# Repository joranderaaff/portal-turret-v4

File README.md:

# Portal Turret v4

A Portal-style turret powered by an ESP32-S3 (Lolin S3 Mini). It detects people with a mmWave radar, opens its wings, extends its guns and tracks targets, complete with sound and lights.

## Repository layout

| Folder | Contents |
| --- | --- |
| `src/` | Firmware (PlatformIO, Arduino framework) |
| `data/` | LittleFS image: audio clips and web UI |
| `3d/` | 3D model (`model.step`) |
| `gerber/` | PCB manufacturing files (MainBoard, DaughterBoard) |
| `images/` | Build guide photos |

## Bill of materials

### Printing
- PLA (Or other material) in white, black and optionally transparent.

### Electronics
- Lolin Wemos S3 Mini
- 4x SG90 180 servo
- 2x SG90 360 servo
- LD2450 Radar Sensor
- ADXL345 Digital 3-axis Accelerometer Module
- MAX98357 Audio amp
- 2x OH49E Hall Effect Sensor - SS49E compatible
- SN74AHCT125N 4-channel Level Converter
- SK6812 Digital 5050 RGB LED Ring
- 5x WS2812 5mm LED
- Small rocker switch
- USB C Breakout Board, 12 * 15 * 1.6mm
- 2x 100nF Ceramic Capacitor 
- 1x 100uF 25V Elektrolytic Capacitor

### Motion
- 604ZZ Ball Bearing - 4x12x4mm
- MYT LM6LUU Linear Ball Bearing - 2 pieces (35mm length)
- 4mm steel rod
- 6mm steel rod

### Cables
- JST PH crimp set OR JST PH headers and pre-crimped JST PH cables
- Pin headers

### Fasteners
- 2mm wood screws
- Super Glue

## Steel Rod Sizes

For the 4mm rods:
- 1x 150mm (enforcing the rear leg)
- 2x 55mm (enforcing the front legs)
- 2x 60mm (wings)
- 1x 43mm (x-axis axle)
- 1x 20mm (z-axis bottom axle)
- 1x 10mm (z-axis top axle)

The bended rods for the legs do not have a very precise length. It's best to bend and cut to length after bending, as this makes the process of getting the correct shape a lot easier.

For the 6mm rods:
- 2x 60mm (wings)

## 3D printing

STEP file contains all 3D printed parts.

[All STL files can be found here.](https://www.printables.com/model/1892132-portal-turret-mk-ii)

## Electronics

Gerber files are included. Order from your favorite PCB manufacturer.

### Pinout

ESP32-S3 GPIO numbers, defined in `src/pins.h`.

| Function | GPIO |
| --- | --- |
| Left / right gun servo | 1 / 2 |
| Left / right wing servo | 4 / 5 |
| Rotate X / Z servo | 6 / 7 |
| Left / right hall sensor (analog) | 8 / 9 |
| Eye LED ring (center) / left gun LEDs / right gun LEDs | 14 / 15 / 16 |
| Radar (ESP RX / ESP TX) | 17 / 18 |
| ADXL345 I2C (SDA / SCL) | 35 / 36 |
| Audio amp I2S (DIN / BCLK / LRCLK) | 10 / 11 / 12 |

### Power

The turret runs on 5 V, from the USB-C board or the power connector. The servos, LED ring, audio amp and radar all share it, so use a supply that can deliver at least 2 A. That figure is a rule of thumb for six SG90 servos plus the LEDs, not a measured value.

## Preperation

The 180 degree servos might not be centered when you purchase them. Make sure you to do this with a servo tester or writing a small Arduino sketch that centers your servos. If you don't have an Arduino board to do this, you could even use the Wemos in a breadboard and use some wires to hook up a servo to calibrate them.

Use the hall sensor to find out what the north and south pole of your magnets are. You'll need to know this to make sure you insert them correctly later in the build.
Again you can use the Wemos to test. Using a breadboard, hook up the sensor to 3.3V, Gnd and one of the analog pins. Read the analog value. When the north pole faces the sensor, the value should increase. If it's the south pole, it should decrease.

## Assembly guide

Here's raw screenshots. Explicit information comes later.

### X axis

| Notes | Images |
| --- | --- |
| Screw the two halves together. |  |
| Insert the LM6LUU and 604ZZ bearings. Screw the gears on the two 360 servos. |  |
| Solder the wires to the hall sensors. Use shrink tubing to protect the leads. Insert the hall sensors into the slots. The beveled face is the front and should point towards the space where the rack gears will slide. |  | 
| Tuck the wires underneath the little lip. This should help with keeping the hall sensors in place. If they don't want to stay seated, a drop of superglue should help. |  | 

### Z axis
| Notes | Images |
| --- | --- |
| Screw on the X Axis gear on a 180 servo. Slide it in place and use the channels to screw it down. |  |
| Attach one side. |  |
| Slide a 4mm rod through the X axis. Add a 4mm shim on both sides. There is a slot in the frame where the rod should fit. |  |
| Scew on the bottom and the other side. |  |
| Use a ziptie to manage all cables. It should hold the following wires: 2 Hall sensors, 2 Wing servos, X Axis servo. |  |

### Bottom
| Notes | Images |
| --- | --- |
| Slide a 180 servo in the mount and screw it secure |  |
| Screw on the Z Axis gear. |  |
| The USB-C board should be glued into place. If you can't get a solid connection with glue, a tiny screw with some heatshrink could be screwed through the D- slot. Make sure the screw does not short D- to ground, hence the heatshrink tubing. Run the wires through the bottom. Make sure to leave enough to route the wires and attach the JST connector. |  |
| Route the two 5V wires to the bottom. One should come from the USB board, the other should go to your power connector. |  |
| The servo wires should also be run through the same channel to go up in the back. |  |
| Run both the servo and power wires through the gantry. Use the little brace to keep them out of the way from the gantry.  |  |

### Eye
| Notes | Images |
| --- | --- |
| Print the flat retina and mold. As PLA gets soft at relatively low temperatures, you can dunk it in boiling water and press it on the mold for the correct shape. Make sure to print the diffuser with very little top/bottom layers and walls, or use transparent filament. Glue in the LED ring and 5mm LED. Bend the 5V and Gnd legs of the LED to the pads of the ring and solder them together. The `D-in` leg should go to the `D-out` pad. Run 3 wires to the `D-in` `5V` and `Gnd` pads of the LED Ring. Keep enough length to run it through the turret. Add a JST connector when you're sure you have enough length. |  |

### Gantry

| Notes | Images |
| --- | --- |
| The gantry consists of 5 different pieces. This is done so you can print with little to no support material. The eye should click in place and stay there without any glue. |  |
| The whole gantry should screw together and give enough rigidity for the build. |  |
| Slide in the gantry and bottom. Make sure to not rotate your servo when assembling, otherwise you'll risk a very big offset in angle. You can calibrate small offsets in the settings. |  |
| Screw in the last screws on the front and back of the gantry to finish the motion system. |  |

### Guns

| Notes | Images |
| --- | --- |
| Prepare the LED harness. You can either use JST connectors or solder directly to the board. Make sure you double check the pads of the board and the legs of your LEDs. I've found that different brands can have a different order in the legs. Please note that the `Data In` leg should go to the `Data In` pad, NOT the `Data Out` pad. |  |
| Attach the lever to a 180 servo. The lever should be a friction fit. Insert it into the gun casing and run the wire as shown. Note that the LED harness is not shown here, but should already be attached to the board. |  |
| There's a hole in the bottom to fasten the servo with a screw. |  |
| Insert the barrels into their housing. This should be a friction fit. The housing screws on the part with one screw. |  |
| Slide in the bottom LED and run the wires to the side and through the clamp in the front. |  |
| Slide in the top LED and run the wires out the top. |  |
| Rotate the lever so it points forward. |  |
| Carefully slide the barrels over the lever. You might need to bend the housing to get it in place. Note that the pictures shows the wires outside of the clamps, this is a render error. |  |
| Slide the barrels back into the housing. They should slide easily. If not, try to move the lever by hand. If the barrels don't move, check the clearance of your parts. |  |
| The top can now be screwed on. |  |
| The front plate should click in place. |  |

### Wings

| Notes | Images |
| --- | --- |
| Add 1mm magnets to the slots of the wing. Mind the polarity! |  |
| Add 1mm magnets to the slots of the the wing frame. Mind the polarity! |  |
| The gun should slide in the designated slot. |  |
| Insert the magnets in the rack gear. They should click in place, but a drop of glue helps. Make sure to mind the polarity!|  |
| Attach the rack gear and secure it with a screw. Glue in the 4mm and 6mm steel rods. |  |

### PCB, Speaker and Radar

| Notes | Images |
| --- | --- |
| PCB, Speaker and Radar should be mounted in the top. Note that the ADXL and Amplifier are missing in this picture. They should be soldered on the PCB. |  |
| There are optional panels to cover the electronics. |  |

### Leg
| Notes | Images |
| --- | --- |
| The legs should be glued together. Use a piece of 4mm rod to strengthen the joint between the "leg" and the "knee" |  |

## Firmware

You can build the firmware with <a href="https://code.visualstudio.com/">Visual Studio Code</a> together with the PlatformIO plugin.

Use the following two commands to flash your Wemos:

Or use these commands if you prefer working in the terminal.

```bash
pio run                # build
pio run -t upload      # flash firmware
pio run -t uploadfs    # flash LittleFS (audio + web UI)
```

Flash both on a new turret: the firmware first, then the filesystem. Run `uploadfs` again whenever something in `data/` changes.

OTA updates are possible once the turret is on your network (`turret.local`) or in its own access point ("Portal Turret", `192.168.4.1`). While an update runs the turret stops moving and the audio pauses.

### First start and WiFi

1. On the first start, and whenever the turret can't join its saved network, it opens the WiFi network "Portal Turret".
2. Connect to it. The WiFi setup page opens by itself, or browse to `http://192.168.4.1`.
3. Pick your network and enter the password. The turret restarts, joins your network and is reachable at `http://turret.local`.
4. If the saved network is out of reach (for example the router is still booting after a power cut), the "Portal Turret" network returns. The turret tries the saved network again every minute, as long as nobody is connected to its access point, and closes the access point once it is back on your network.

The access point is open by default. To protect it, enter 8 or more characters as "Access Point Password" on the Settings page and restart the turret. The access point keeps that password when you reset the settings to their defaults, so it can't fall back to open by accident.

### Web interface

| Page | What it does |
| --- | --- |
| Home | Live radar, accelerometer graphs and the turret's message log. |
| Control | Start the turret by hand. |
| Remote | Aim with a joystick, open/close the wings, fire, party mode. |
| Settings | All settings, Restart, reset to defaults, enable multitarget on the radar. |
| WiFi | Pick the network the turret joins. |
| Diagnose | Move every servo raw, read the hall sensors, test LEDs and audio. |

Settings take effect as soon as you save them. Only the network settings (WiFi, access point password) need a restart: use the Restart button on the Settings page.

Remote and Diagnose stop all automatic behaviour. Press Resume on either page to hand control back: the turret centers the gantry, closes the wings and starts over. A power cycle does the same.

## Calibration

When connecting to the web portal, there is a `Settings` page. Most of these settings are tweaked already, but you might need a few to get your turret to work perfectly:
You can use the `Diagnose` page to find the exact values you want to use (the hall sensor readings help with Gun Hall Min/Max).

- Angle offset X: Use this to make sure the wings are pointing forward when the turret is idle.
- Angle offset Z: Use this to center the gantry when the turret is idle.
- Gun Hall Min/Max: The treshold of the hall sensor that triggers the Open/Closed state of the wings.

The other parameters are less important, but you can play around with them to suit your needs.

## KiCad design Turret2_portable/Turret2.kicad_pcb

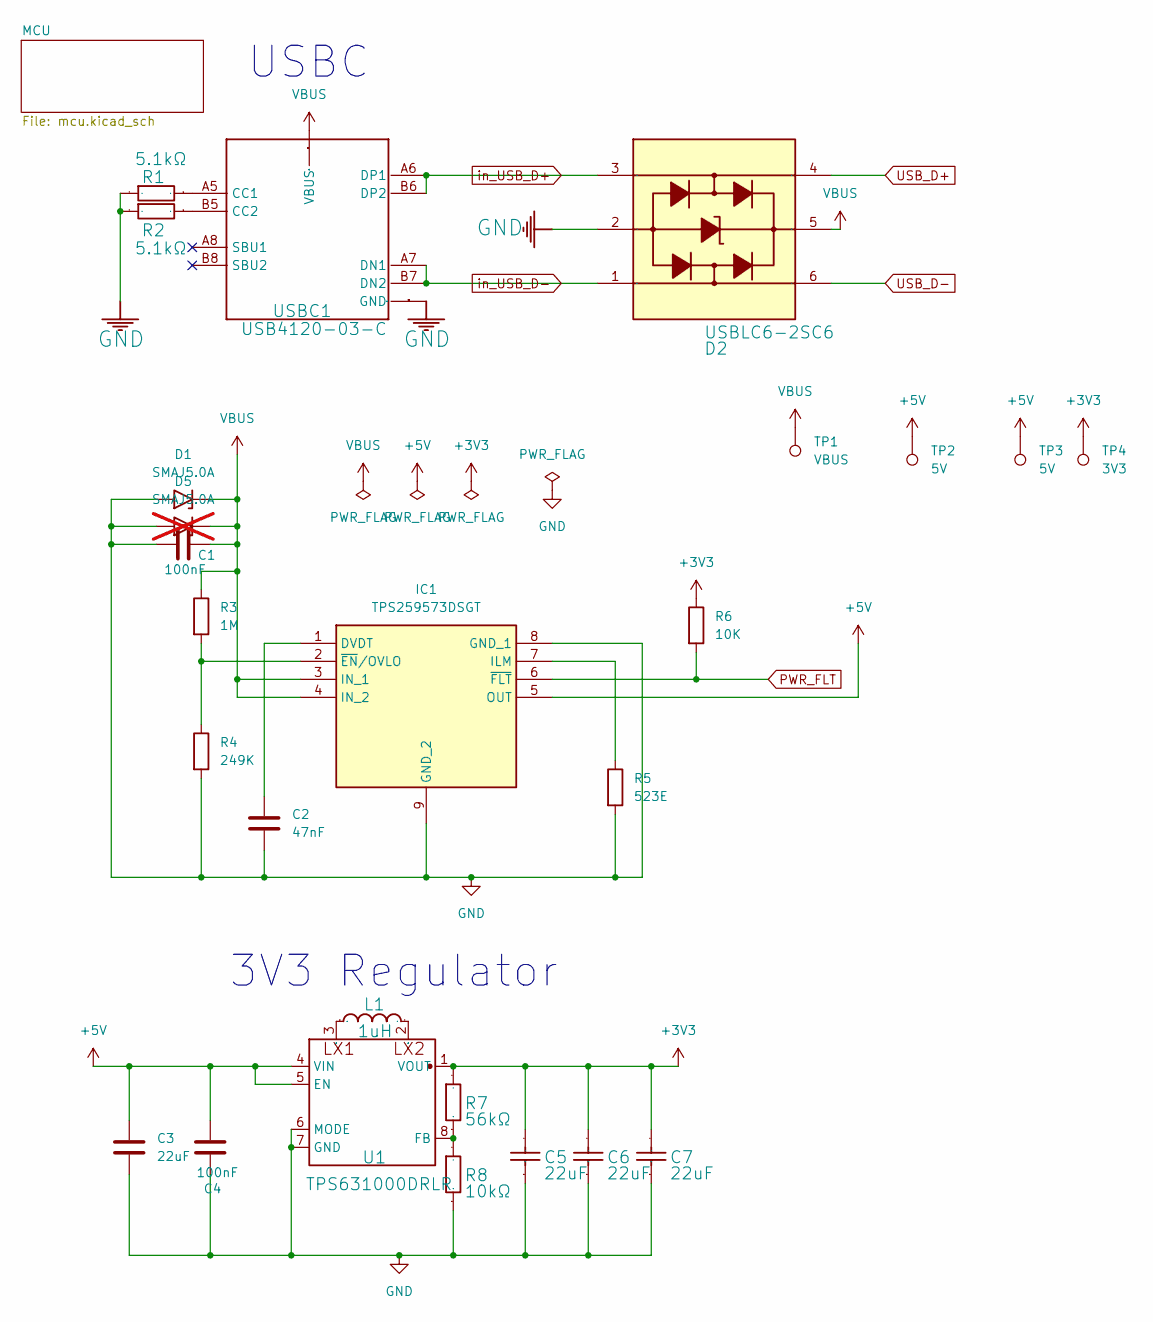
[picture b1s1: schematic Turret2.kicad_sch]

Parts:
C1, C4: 100nF; C_0603_1608Metric
C2: 47nF; C_0603_1608Metric
C3: 22uF; C_1210_3225Metric
C5, C6, C7: 22uF; C_1210_3225Metric; Manufacturer Part MCAST32MSB7226KPNA01
D1: SMAJ5.0A; D_SMA
D2: USBLC6-2SC6; SOT-23-6; Manufacturer Part USBLC6-2SC6
D5: SMAJ5.0A; D_SMA; not fitted
IC1: TPS259573DSGT; Texas_DSG0008A_WSON-8-1EP_2x2mm_P0.5mm_EP0.9x1.6mm_ThermalV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; Mouser Part Number 595-TPS259573DSGT
L1: 1uH; L_Changjiang_FTC303020D; Manufacturer Part FTC303020D1R0MBCA
R1, R2: 5.1kΩ; R_0603_1608Metric; Manufacturer Part 0402WGF5101TCE
R3: 1M; R_0603_1608Metric
R4: 249K; R_0603_1608Metric
R5: 523E; R_0603_1608Metric
R6: 10K; R_0603_1608Metric
R7: 56kΩ; R_0603_1608Metric; Manufacturer Part 0603WAF5602T5E
R8: 10kΩ; R_0603_1608Metric; Manufacturer Part 0402WGF1002TCE
TP1: VBUS; TestPoint_Pad_D1.0mm
TP2, TP3: 5V; TestPoint_Pad_D1.0mm
TP4: 3V3; TestPoint_Pad_D1.0mm
U1: TPS631000DRLR; SOTFL50P160X60-8N; Manufacturer Part TPS631000DRLR
USBC1: USB4120-03-C; USB412003C; Manufacturer Part USB4120-03-C

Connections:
+3V3: C5.2, C6.2, C7.2, R6.1, R7.2, TP4.1 (1_1), U1.1 (VOUT); also elsewhere on the board
+5V: C3.1, C4.1, IC1.5 (OUT), TP2.1 (1_1), TP3.1 (1_1), U1.4 (VIN), U1.5 (EN); also elsewhere on the board
GND: C1.1, C2.2, C3.2, C4.2, C5.1, C6.1, C7.1, D1.2 (A2), D2.2, D5.2 (A2), IC1.8 (GND_1), IC1.9 (GND_2), R1.2, R2.2, R4.2, R5.2, R8.1, U1.6 (MODE), U1.7 (GND), USBC1.A1 (GND), USBC1.A12 (GND), USBC1.B1 (GND), USBC1.B12 (GND), USBC1.MH1 (GND), USBC1.MH2 (GND), USBC1.MH3 (GND), USBC1.MH4 (GND); also elsewhere on the board
unnamed: C2.1, IC1.1 (DVDT)
unnamed: IC1.7 (ILM), R5.1
unnamed: IC1.2 (~EN/OVLO), R3.2, R4.1
unnamed: R7.1, R8.2, U1.8 (FB)
unnamed: L1.1, U1.3 (LX1)
unnamed: L1.2, U1.2 (LX2)
unnamed: R1.1, USBC1.A5 (CC1)
unnamed: R2.1, USBC1.B5 (CC2)
PWR_FLT: IC1.6 (~FLT), R6.2; also elsewhere on the board
USB_D+: D2.4; also elsewhere on the board
USB_D-: D2.6; also elsewhere on the board
VBUS: C1.2, D1.1 (A1), D2.5, D5.1 (A1), IC1.3 (IN_1), IC1.4 (IN_2), R3.1, TP1.1 (1_1), USBC1.A4 (VBUS), USBC1.A9 (VBUS), USBC1.B4 (VBUS), USBC1.B9 (VBUS); also elsewhere on the board
in_USB_D+: D2.3, USBC1.A6 (DP1), USBC1.B6 (DP2); also elsewhere on the board
in_USB_D-: D2.1, USBC1.A7 (DN1), USBC1.B7 (DN2); also elsewhere on the board

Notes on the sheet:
3V3 Regulator
USBC

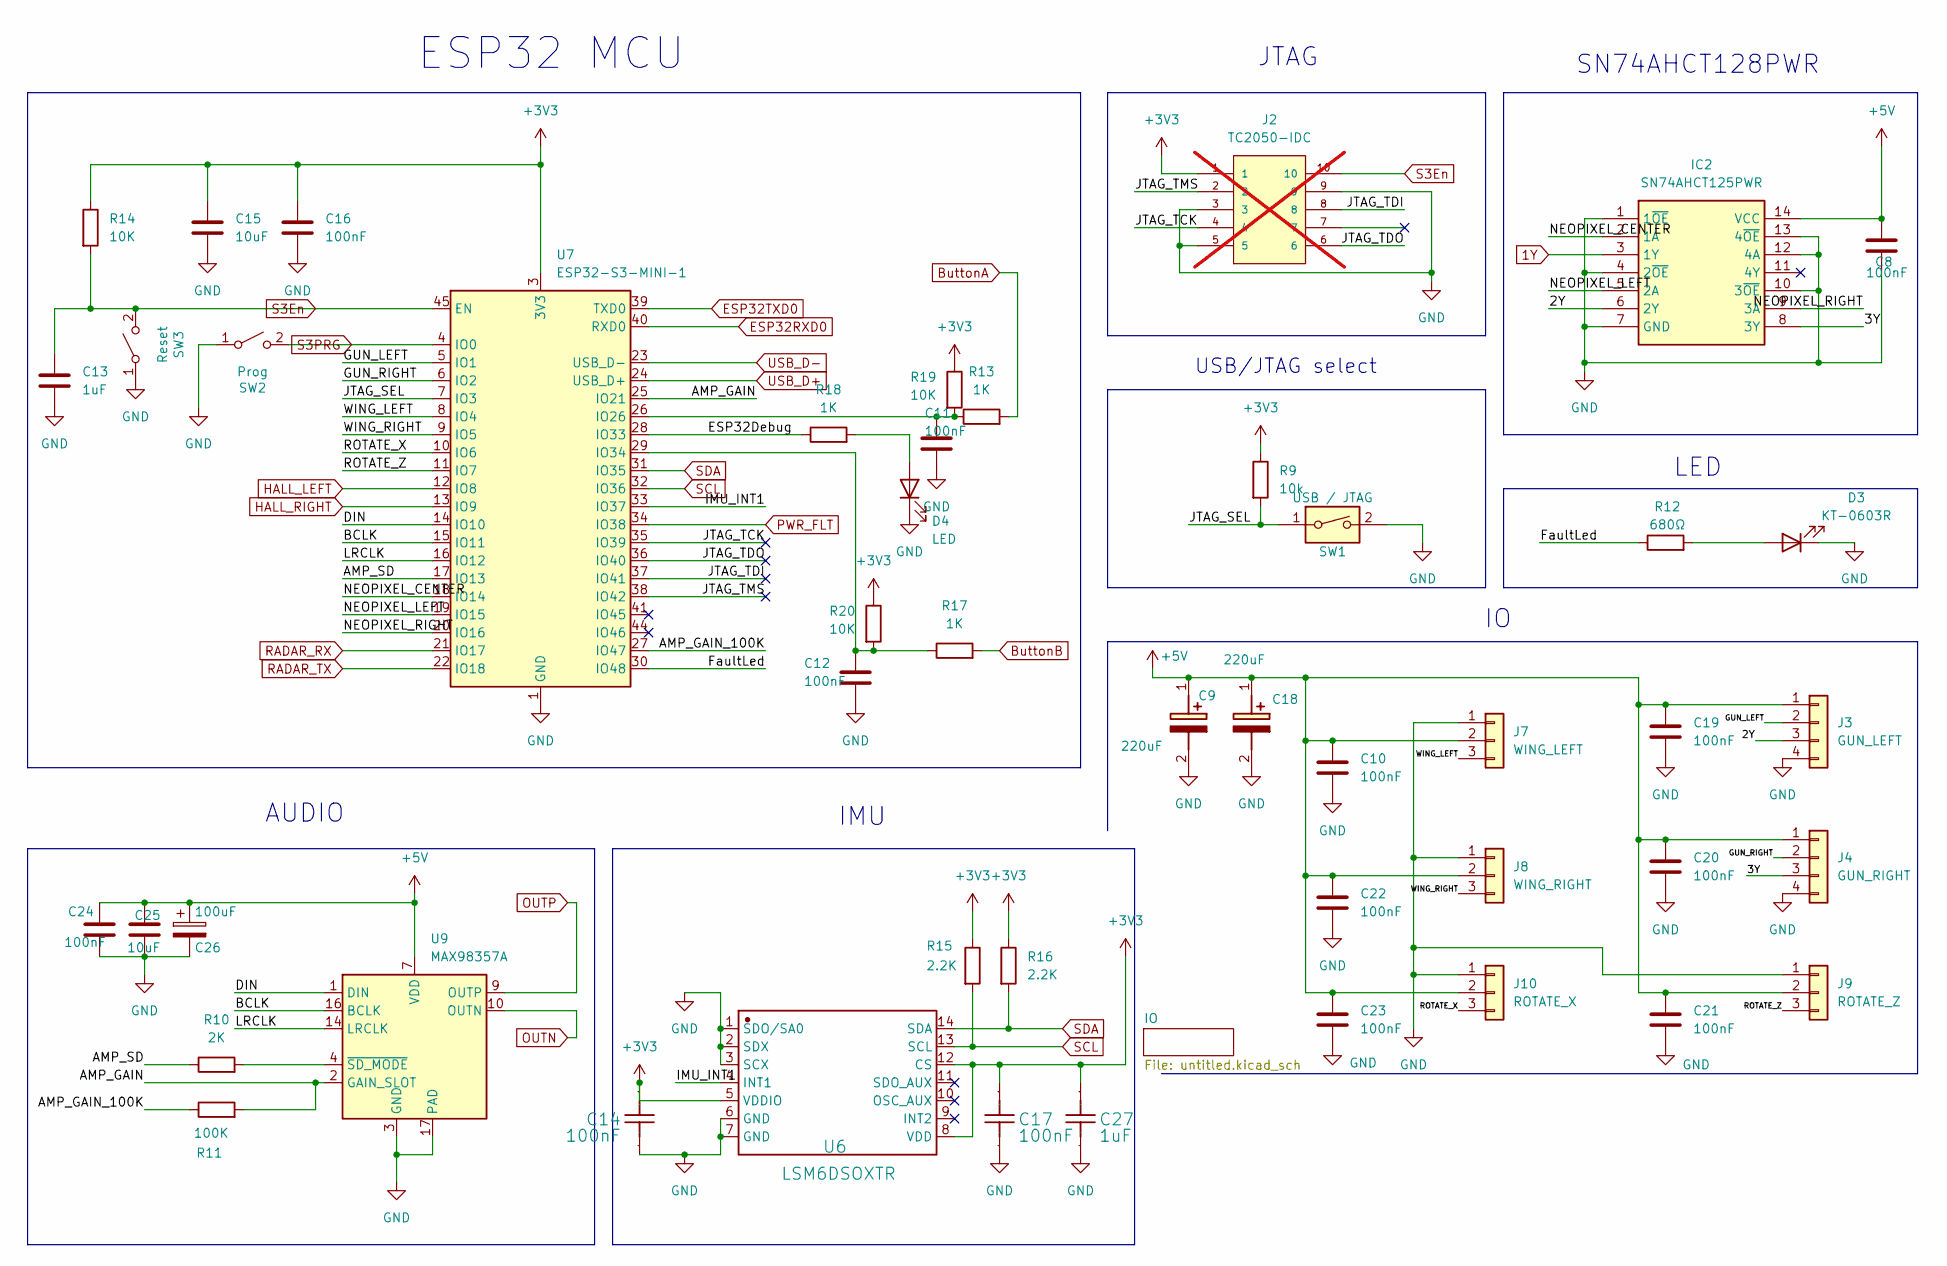
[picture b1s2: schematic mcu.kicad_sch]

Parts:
C8, C10, C11, C12, C16, C19, C20, C21, C22, C23, C24: 100nF; C_0603_1608Metric
C9, C18: 220uF; CP_Elec_6.3x5.9; Mouser Part Number 16SVPG220M
C13: 1uF; C_0603_1608Metric
C14, C17: 100nF; C_0603_1608Metric; Manufacturer Part CL05B104KO5NNNC
C15, C25: 10uF; C_0805_2012Metric
C26: 100uF; CP_Elec_6.3x7.7
C27: 1uF; C_0603_1608Metric; Manufacturer Part CL05B104KO5NNNC
D3: KT-0603R; LED_0603_1608Metric
D4: LED; LED_0603_1608Metric
IC2: SN74AHCT125PWR; TSSOP-14_4.4x5mm_P0.65mm; Mouser Part Number 595-SN74AHCT125PWR
J2: TC2050-IDC; TAG-CONNECT_TC2050-IDC; PARTREV A; not fitted
J3: GUN_LEFT; JST_PH_B4B-PH-K_1x04_P2.00mm_Vertical
J4: GUN_RIGHT; JST_PH_B4B-PH-K_1x04_P2.00mm_Vertical
J7: WING_LEFT; JST_PH_B3B-PH-K_1x03_P2.00mm_Vertical
J8: WING_RIGHT; JST_PH_B3B-PH-K_1x03_P2.00mm_Vertical
J9: ROTATE_Z; JST_PH_B3B-PH-K_1x03_P2.00mm_Vertical
J10: ROTATE_X; JST_PH_B3B-PH-K_1x03_P2.00mm_Vertical
R9: 10k; R_0603_1608Metric
R10: 2K; R_0603_1608Metric
R11: 100K; R_0603_1608Metric
R12: 680Ω; R_0603_1608Metric
R13, R17: 1K; R_1206_3216Metric_Pad1.30x1.75mm_HandSolder
R14, R19, R20: 10K; R_0603_1608Metric
R15, R16: 2.2K; R_0603_1608Metric
R18: 1K; R_0603_1608Metric
SW1: USB / JTAG; SW_DIP_SPSTx01_Slide_Copal_CHS-01A_W5.08mm_P1.27mm_JPin
SW2: Prog; SW_SPST_TS-1088-xR020
SW3: Reset; SW_SPST_TS-1088-xR020
U6: LSM6DSOXTR; LGA-14_1; Manufacturer Part LSM6DSOXTR
U7: ESP32-S3-MINI-1; ESP32-S2-MINI-1
U9: MAX98357A; 21-0136I_T1633-4_MXM

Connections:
1Y: IC2.3 (1Y); also elsewhere on the board
+3V3: C14.1, C15.1, C16.1, C17.1, C27.1, J2.1, R9.1, R14.1, R15.1, R16.1, R19.1, R20.1, U6.5 (VDDIO), U6.8 (VDD), U6.12 (CS), U7.3 (3V3); also elsewhere on the board
+5V: C8.1, C9.1 (+), C10.1, C18.1 (+), C19.1, C20.1, C21.1, C22.1, C23.1, C24.1, C25.1, C26.1, IC2.14 (VCC), J3.1, J4.1, J7.2, J8.2, J9.2, J10.2, U9.7 (VDD), U9.8 (VDD); also elsewhere on the board
/MCU/2Y: IC2.6 (2Y), J3.3
/MCU/3Y: IC2.8 (3Y), J4.3
/MCU/AMP_GAIN: R11.2, U7.25 (IO21), U9.2 (GAIN_SLOT)
/MCU/AMP_GAIN_100K: R11.1, U7.27 (IO47)
/MCU/AMP_SD: R10.1, U7.17 (IO13)
/MCU/BCLK: U7.15 (IO11), U9.16 (BCLK)
/MCU/DIN: U7.14 (IO10), U9.1 (DIN)
/MCU/ESP32Debug: R18.1, U7.28 (IO33)
/MCU/FaultLed: R12.1, U7.30 (IO48)
/MCU/GUN_LEFT: J3.2, U7.5 (IO1)
/MCU/GUN_RIGHT: J4.2, U7.6 (IO2)
/MCU/IMU_INT1: U6.4 (INT1), U7.33 (IO37)
/MCU/JTAG_SEL: R9.2, SW1.1, U7.7 (IO3)
/MCU/JTAG_TCK: J2.4, U7.35 (IO39)
/MCU/JTAG_TDI: J2.8, U7.37 (IO41)
/MCU/JTAG_TDO: J2.6, U7.36 (IO40)
/MCU/JTAG_TMS: J2.2, U7.38 (IO42)
/MCU/LRCLK: U7.16 (IO12), U9.14 (LRCLK)
/MCU/NEOPIXEL_CENTER: IC2.2 (1A), U7.18 (IO14)
/MCU/NEOPIXEL_LEFT: IC2.5 (2A), U7.19 (IO15)
/MCU/NEOPIXEL_RIGHT: IC2.9 (3A), U7.20 (IO16)
/MCU/ROTATE_X: J10.3, U7.10 (IO6)
/MCU/ROTATE_Z: J9.3, U7.11 (IO7)
/MCU/WING_LEFT: J7.3, U7.8 (IO4)
/MCU/WING_RIGHT: J8.3, U7.9 (IO5)
ButtonA: R13.2; also elsewhere on the board
ButtonB: R17.2; also elsewhere on the board
ESP32RXD0: U7.40 (RXD0); also elsewhere on the board
ESP32TXD0: U7.39 (TXD0); also elsewhere on the board
GND: C8.2, C9.2 (-), C10.2, C11.1, C12.1, C13.2, C14.2, C15.2, C16.2, C17.2, C18.2 (-), C19.2, C20.2, C21.2, C22.2, C23.2, C24.2, C25.2, C26.2, C27.2, D3.1 (K), D4.1 (K), IC2.1 (1~OE), IC2.4 (2~OE), IC2.7 (GND), IC2.10 (3~OE), IC2.12 (4A), IC2.13 (4~OE), J2.3, J2.5, J2.9, J3.4, J4.4, J7.1, J8.1, J9.1, J10.1, SW1.2, SW2.1 (A), SW3.1 (A), U6.1 (SDO/SA0), U6.2 (SDX), U6.3 (SCX), U6.6 (GND), U6.7 (GND), U7.1 (GND), U7.2 (GND), U7.42 (GND), U7.43 (GND), U7.46 (GND), U7.47 (GND), U7.48 (GND), U7.49 (GND), U7.50 (GND), U7.51 (GND), U7.52 (GND), U7.53 (GND), U7.54 (GND), U7.55 (GND), U7.56 (GND), U7.57 (GND), U7.58 (GND), U7.59 (GND), U7.60 (GND), U7.61 (GND), U7.62 (GND), U7.63 (GND), U7.64 (GND), U7.65 (GND), U9.3 (GND), U9.11 (GND), U9.15 (GND), U9.17 (PAD); also elsewhere on the board
HALL_LEFT: U7.12 (IO8); also elsewhere on the board
HALL_RIGHT: U7.13 (IO9); also elsewhere on the board
unnamed: D3.2 (A), R12.2
unnamed: D4.2 (A), R18.2
unnamed: C11.2, R13.1, R19.2, U7.26 (IO26)
unnamed: C12.2, R17.1, R20.2, U7.29 (IO34)
unnamed: R10.2, U9.4 (~SD_MODE)
OUTN: U9.10 (OUTN); also elsewhere on the board
OUTP: U9.9 (OUTP); also elsewhere on the board
PWR_FLT: U7.34 (IO38); also elsewhere on the board
RADAR_RX: U7.21 (IO17); also elsewhere on the board
RADAR_TX: U7.22 (IO18); also elsewhere on the board
S3En: C13.1, J2.10, R14.2, SW3.2 (B), U7.45 (EN); also elsewhere on the board
S3PRG: SW2.2 (B), U7.4 (IO0); also elsewhere on the board
SCL: R15.2, U6.13 (SCL), U7.32 (IO36); also elsewhere on the board
SDA: R16.2, U6.14 (SDA), U7.31 (IO35); also elsewhere on the board
USB_D+: U7.24 (USB_D+); also elsewhere on the board
USB_D-: U7.23 (USB_D-); also elsewhere on the board

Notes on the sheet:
JTAG
USB/JTAG select
LED
ESP32 MCU
AUDIO
IMU
SN74AHCT128PWR

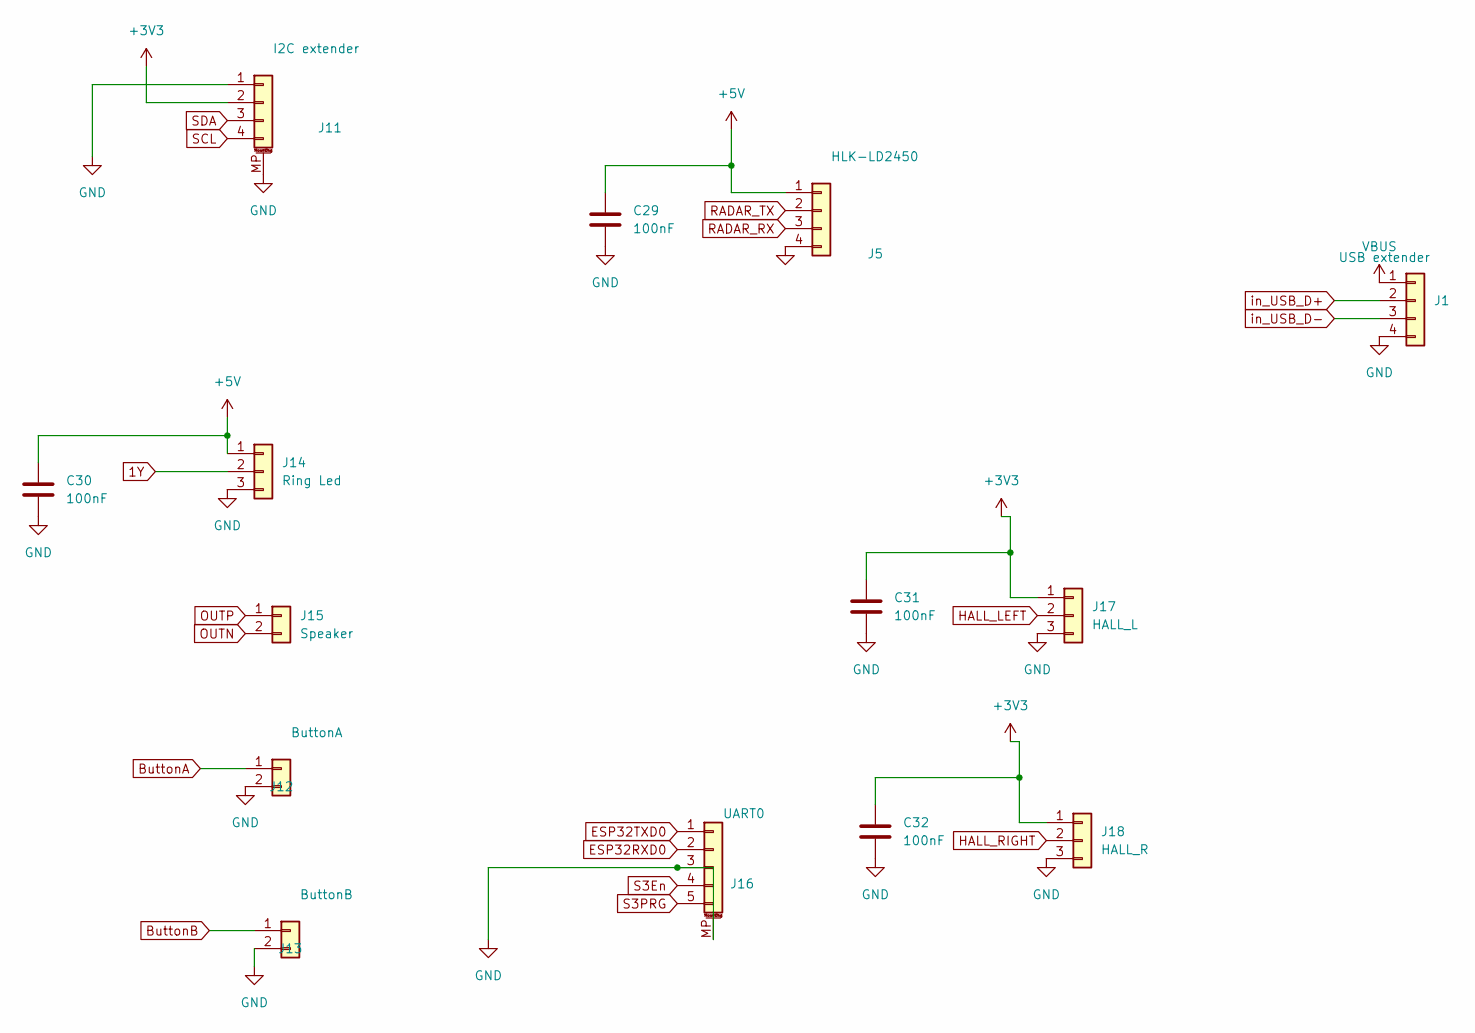
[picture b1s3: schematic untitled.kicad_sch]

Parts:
C29, C30, C31, C32: 100nF; C_0603_1608Metric
J1: USB extender; JST_PH_B4B-PH-K_1x04_P2.00mm_Vertical
J5: HLK-LD2450; JST_PH_B4B-PH-K_1x04_P2.00mm_Vertical
J11: I2C extender; JST_SH_SM04B-SRSS-TB_1x04-1MP_P1.00mm_Horizontal
J12: ButtonA; SHDR2W50P0X200_1X2_590X450X600P
J13: ButtonB; SHDR2W50P0X200_1X2_590X450X600P
J14: Ring Led; JST_PH_B3B-PH-K_1x03_P2.00mm_Vertical
J15: Speaker; TerminalBlock_Phoenix_PT-1,5-2-3.5-H_1x02_P3.50mm_Horizontal
J16: UART0; JST_SH_SM05B-SRSS-TB_1x05-1MP_P1.00mm_Horizontal
J17: HALL_L; JST_PH_B3B-PH-K_1x03_P2.00mm_Vertical
J18: HALL_R; JST_PH_B3B-PH-K_1x03_P2.00mm_Vertical

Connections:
1Y: J14.2; also elsewhere on the board
+3V3: C31.1, C32.1, J11.2, J17.1, J18.1; also elsewhere on the board
+5V: C29.1, C30.1, J5.1, J14.1; also elsewhere on the board
ButtonA: J12.1; also elsewhere on the board
ButtonB: J13.1; also elsewhere on the board
ESP32RXD0: J16.2; also elsewhere on the board
ESP32TXD0: J16.1; also elsewhere on the board
GND: C29.2, C30.2, C31.2, C32.2, J1.4, J5.4, J11.1, J11.MP (MountPin), J12.2, J13.2, J14.3, J16.3, J16.MP (MountPin), J17.3, J18.3; also elsewhere on the board
HALL_LEFT: J17.2; also elsewhere on the board
HALL_RIGHT: J18.2; also elsewhere on the board
OUTN: J15.2; also elsewhere on the board
OUTP: J15.1; also elsewhere on the board
RADAR_RX: J5.3; also elsewhere on the board
RADAR_TX: J5.2; also elsewhere on the board
S3En: J16.4; also elsewhere on the board
S3PRG: J16.5; also elsewhere on the board
SCL: J11.4; also elsewhere on the board
SDA: J11.3; also elsewhere on the board
VBUS: J1.1; also elsewhere on the board
in_USB_D+: J1.2; also elsewhere on the board
in_USB_D-: J1.3; also elsewhere on the board

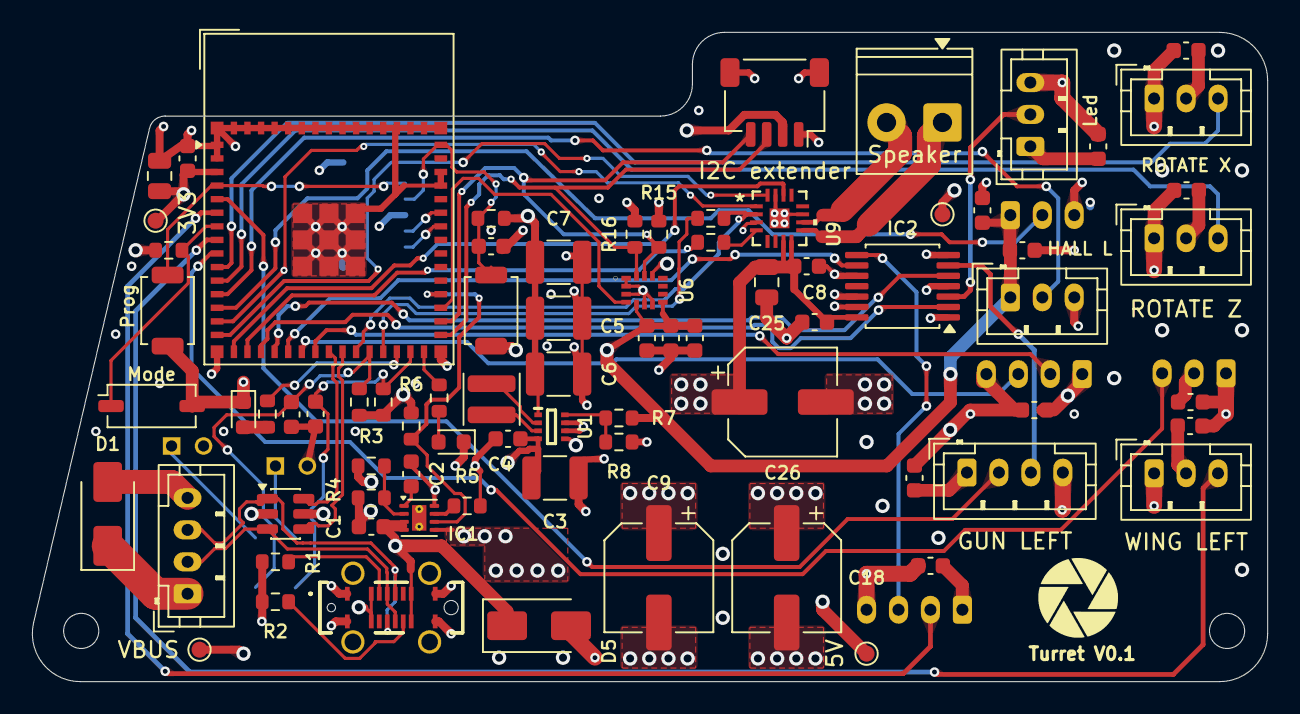
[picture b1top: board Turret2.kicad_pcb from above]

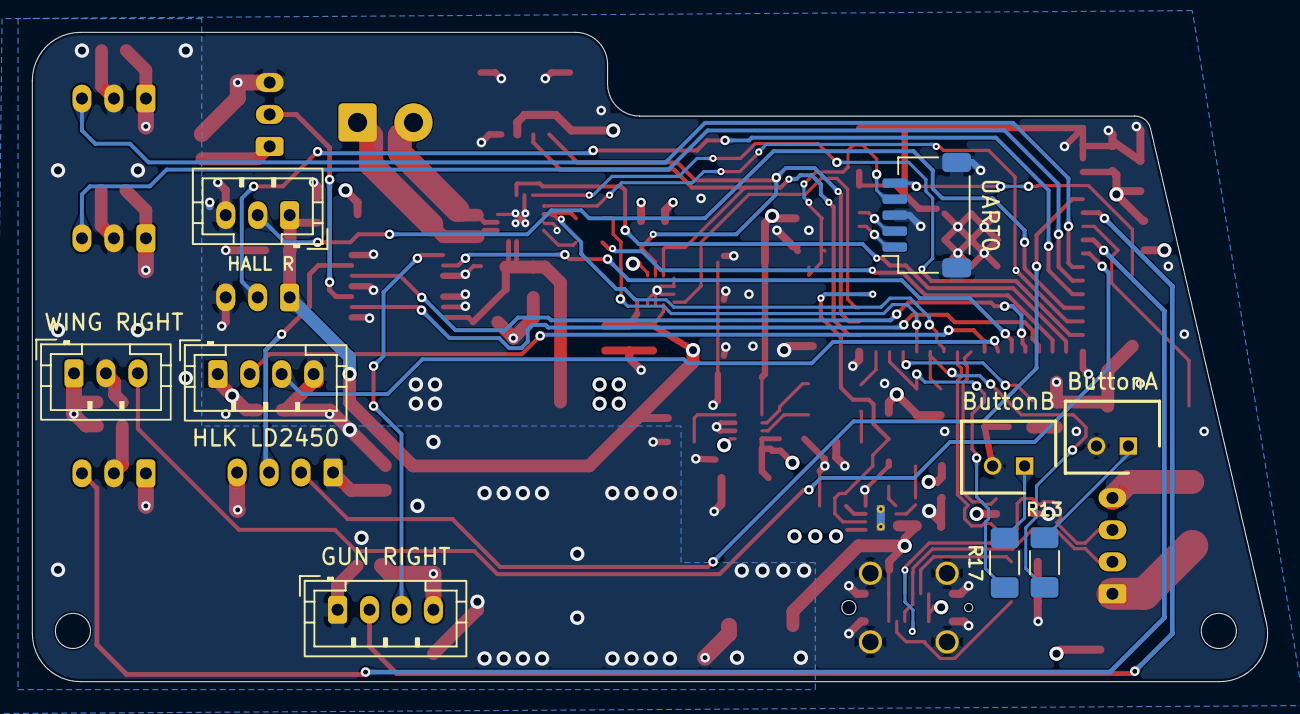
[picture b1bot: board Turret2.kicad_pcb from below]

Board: 4 copper layers, 77.3 x 40.6 mm, 90 parts (9 on the bottom side), 58 nets.

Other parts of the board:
H1, H2: MountingHole 2.2mm NPTH; MountingHole_2.2mm_M2
Turret V0.1: LOGO; gun5

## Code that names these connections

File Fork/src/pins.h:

#define PIN_GUN_LEFT 1  // PWM
#define PIN_GUN_RIGHT 2  // PWM
#define PIN_WING_LEFT 4  // PWM
#define PIN_WING_RIGHT 5  // PWM
#define PIN_ROTATE_X 6  // PWM
#define PIN_ROTATE_Z 7  // PWM
#define PIN_HALL_LEFT 8  // ADC
#define PIN_HALL_RIGHT 9  // ADC
#define PIN_NEOPIXEL_CENTER 14  // PWM
#define PIN_NEOPIXEL_LEFT 15  // PWM
#define PIN_NEOPIXEL_RIGHT 16  // PWM
#define PIN_RADAR_RX 17  // UART_RX
#define PIN_RADAR_TX 18  // UART_TX
#define PIN_SDA 35  // I2C_SDA
#define PIN_SCL 36  // I2C_SCL
#define PIN_DIN 10  // Custom
#define PIN_BCLK 11  // Custom
#define PIN_LRCLK 12  // Custom
